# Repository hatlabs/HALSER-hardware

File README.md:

# Hat Labs Serial Interface Device (HALSER)

This repository contains the Hat Labs Serial Interface Device (HALSER) hardware design. HALSER is a powerful microcontroller development board designed for marine environments that allows interfacing with legacy NMEA 0183, RS-232 and UART devices.

Since the board has native WiFi and NMEA 2000 compatible CAN bus connectivity, it can be used to create boards with either Signal K or native NMEA 2000 connectivity (or both!).

## Features

The main design features include:

- Built around ESP32-C3, a powerful 32-bit microcontroller with 4 MB of flash
- Wide-range 5-32 V power input with surge protection
- NMEA 2000 compatible CAN interface (4-pin pluggable terminal block screw connector)
- One transmitting and one receiving RS-485 interface for bidirectional communication with NMEA 0183 devices (3-pin pluggable terminal block screw connectors)
- One RS-232 interface for communication with legacy devices (3-pin pluggable terminal block screw connector)
- One UART interface for general-purpose communication (3-pin pluggable terminal block screw connector). UART is 5V tolerant and the output voltage can be set to 3.3V or 5V with a jumper.
- 1-Wire interface (3-pin 2.54 mm header)
- I2C interface with a 4-pin 2.54 mm header
- USB type C interface for programming and serial communication
- All above interfaces with proper electromagnetic compatibilty (EMC) design -- the device won't interfere with navigational devices or radio equipment
- All available general-purpose input/output (GPIO) pins broken out to a separate header
- Board designed to fit low-cost waterproof 100x68x50 mm enclosures

Rendering of a version 1.0.0 board:

<!--
Front side.

Back side.

-->

## Getting HALSER

HALSER will be available for purchase at the [Hat Labs web store](https://shop.hatlabs.fi/).

## Documentation

HALSER documentation will be available at the [project GitHub Pages](https://docs.hatlabs.fi/halser/).

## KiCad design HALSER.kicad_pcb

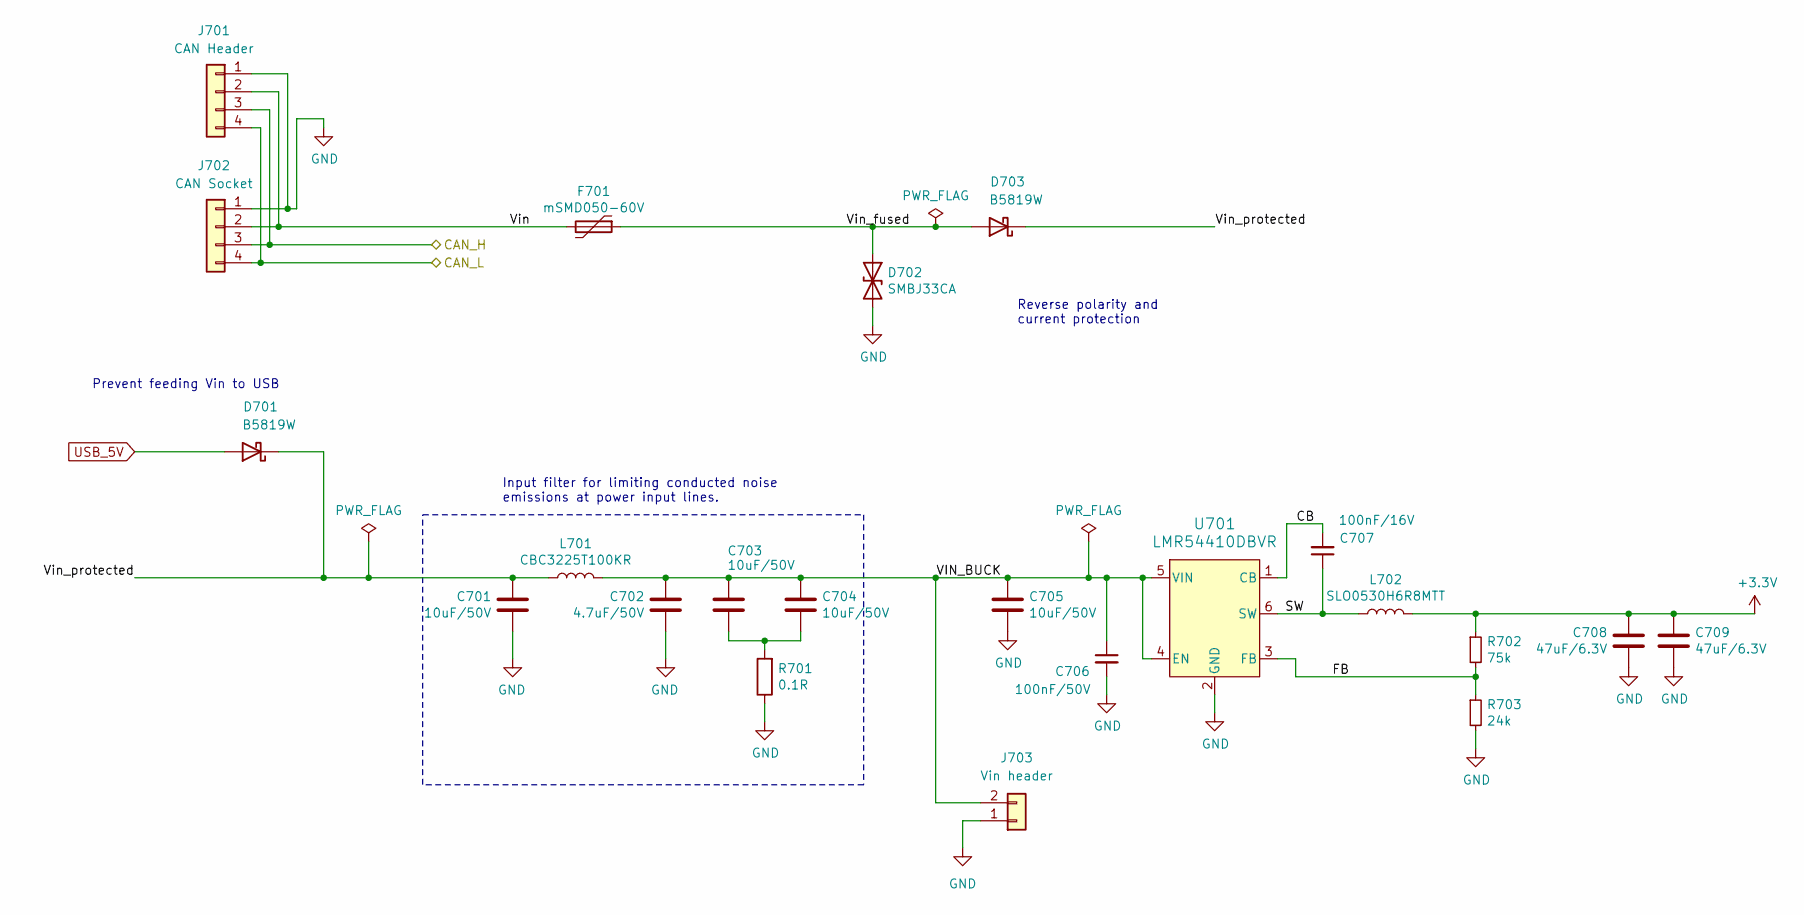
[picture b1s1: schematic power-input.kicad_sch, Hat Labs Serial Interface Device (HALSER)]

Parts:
C701, C703, C704, C705: 10uF/50V; C_1206_3216Metric; LCSC C13585
C702: 4.7uF/50V; C_0805_2012Metric; LCSC C1710
C706: 100nF/50V; C_0603_1608Metric; LCSC C14663
C707: 100nF/16V; C_0402_1005Metric; LCSC C1525
C708, C709: 47uF/6.3V; C_0805_2012Metric; LCSC C16780
D701, D703: B5819W; D_SOD-123; LCSC C8598
D702: SMBJ33CA; D_SMB; LCSC C114000
F701: mSMD050-60V; Fuse_1812_4532Metric; LCSC C70113
J701: CAN Header; PinHeader_1x04_P2.54mm_Vertical; LCSC C7430360
J702: CAN Socket; PhoenixContact_MCV_1,5_4-G-3.81_1x04_P3.81mm_Vertical; LCSC C8410
J703: Vin header; PinHeader_1x02_P2.54mm_Vertical; LCSC C492401
L701: CBC3225T100KR; L_1210_3225Metric; LCSC C90321
L702: SLO0530H6R8MTT; L_Chilisin_BMRA00050530; LCSC C325965
R701: 0.1R; R_0603_1608Metric; LCSC C3013345
R702: 75k; R_0402_1005Metric; LCSC C208939
R703: 24k; R_0402_1005Metric; LCSC C25769
U701: LMR54410DBVR; SOT-23-6; LCSC C3200265

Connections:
+3.3V: C708.1, C709.1, L702.2, R702.1; also elsewhere on the board
/CAN_H: J701.3, J702.3; also elsewhere on the board
/CAN_L: J701.4, J702.4; also elsewhere on the board
/Power input/CB: C707.2, U701.1 (CB)
/Power input/FB: R702.2, R703.1, U701.3 (FB)
/Power input/SW: C707.1, L702.1, U701.6 (SW)
/Power input/VIN_BUCK: C702.2, C703.1, C704.1, C705.1, C706.1, J703.2, L701.2, U701.4 (EN), U701.5 (VIN)
/Power input/Vin: F701.2, J701.2, J702.2
/Power input/Vin_fused: D702.1 (A1), D703.2 (A), F701.1
/Power input/Vin_protected: C701.1, D701.1 (K), D703.1 (K), L701.1
GND: C701.2, C702.1, C705.2, C706.2, C708.2, C709.2, D702.2 (A2), J701.1, J702.1, J703.1, R701.1, R703.2, U701.2 (GND); also elsewhere on the board
unnamed: C703.2, C704.2, R701.2
USB_5V: D701.2 (A); also elsewhere on the board

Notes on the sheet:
Input filter for limiting conducted noise emissions at power input lines.
Prevent feeding Vin to USB
Reverse polarity and current protection

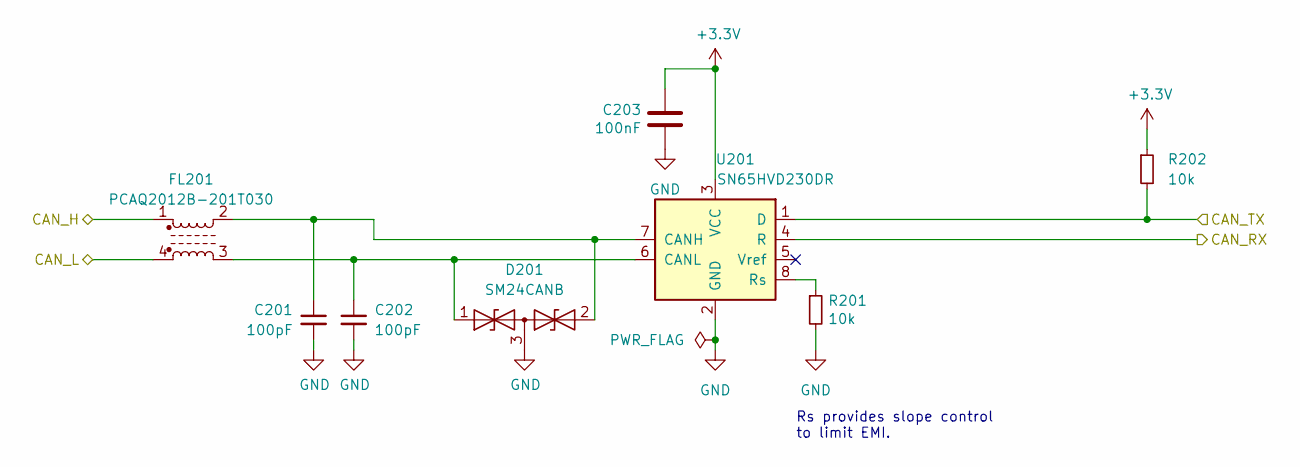
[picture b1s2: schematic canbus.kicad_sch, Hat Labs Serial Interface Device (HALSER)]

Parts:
C201, C202: 100pF; C_0603_1608Metric; LCSC C14858
C203: 100nF; C_0402_1005Metric; LCSC C1525
D201: SM24CANB; SOT-23; LCSC C19185908
FL201: PCAQ2012B-201T030; L_CommonModeChoke_PCAQ2012B; LCSC C2926967
R201, R202: 10k; R_0402_1005Metric; LCSC C25744
U201: SN65HVD230DR; SOIC-8_3.9x4.9mm_P1.27mm; LCSC C12084

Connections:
+3.3V: C203.1, R202.1, U201.3 (VCC); also elsewhere on the board
/CAN_H: FL201.1; also elsewhere on the board
/CAN_L: FL201.4; also elsewhere on the board
/CAN_RX: U201.4 (R); also elsewhere on the board
/CAN_TX: R202.2, U201.1 (D); also elsewhere on the board
GND: C201.2, C202.2, C203.2, D201.3 (common), R201.2, U201.2 (GND); also elsewhere on the board
unnamed: C202.1, D201.1 (A1), FL201.3, U201.6 (CANL)
unnamed: C201.1, D201.2 (A2), FL201.2, U201.7 (CANH)
unnamed: R201.1, U201.8 (Rs)

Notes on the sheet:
Rs provides slope control to limit EMI.

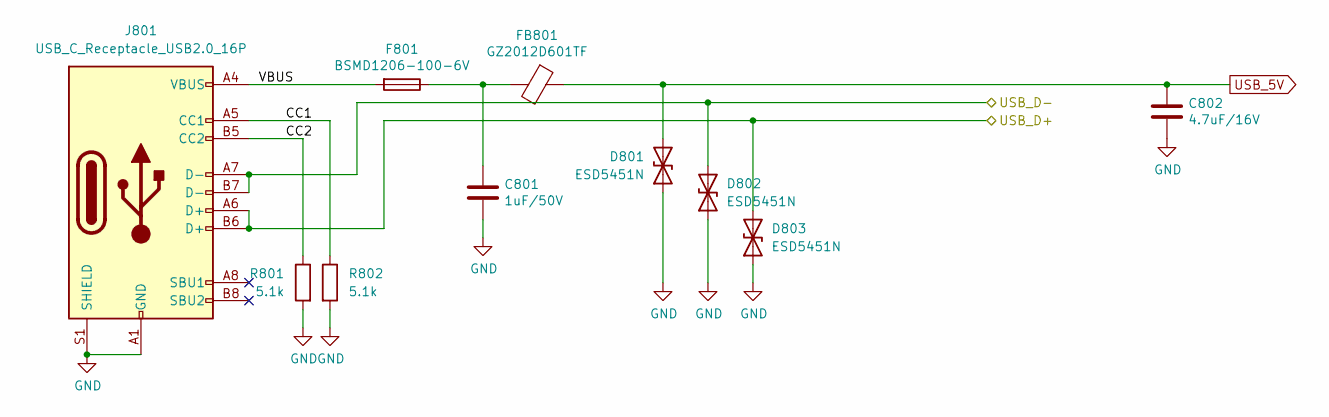
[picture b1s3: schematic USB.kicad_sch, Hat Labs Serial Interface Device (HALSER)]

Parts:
C801: 1uF/50V; C_0603_1608Metric; LCSC C15849
C802: 4.7uF/16V; C_0603_1608Metric; LCSC C19666
D801, D802, D803: ESD5451N; D_0402_1005Metric; LCSC C2936977
F801: BSMD1206-100-6V; Fuse_1206_3216Metric; LCSC C883129
FB801: GZ2012D601TF; L_0805_2012Metric; LCSC C1017
J801: USB_C_Receptacle_USB2.0_16P; Shou Han Type-C 16P LTH6.8; LCSC C5187468
R801, R802: 5.1k; R_0402_1005Metric; LCSC C25905

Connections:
/USB/CC1: J801.A5 (CC1), R802.1
/USB/CC2: J801.B5 (CC2), R801.1
/USB/VBUS: F801.2, J801.A4 (VBUS), J801.A9 (VBUS), J801.B4 (VBUS), J801.B9 (VBUS)
/USB_D+: D803.2 (A2), J801.A6 (D+), J801.B6 (D+); also elsewhere on the board
/USB_D-: D802.2 (A2), J801.A7 (D-), J801.B7 (D-); also elsewhere on the board
GND: C801.2, C802.2, D801.1 (A1), D802.1 (A1), D803.1 (A1), J801.A1 (GND), J801.A12 (GND), J801.B1 (GND), J801.B12 (GND), J801.S1 (SHIELD), R801.2, R802.2; also elsewhere on the board
unnamed: C801.1, F801.1, FB801.2
USB_5V: C802.1, D801.2 (A2), FB801.1; also elsewhere on the board

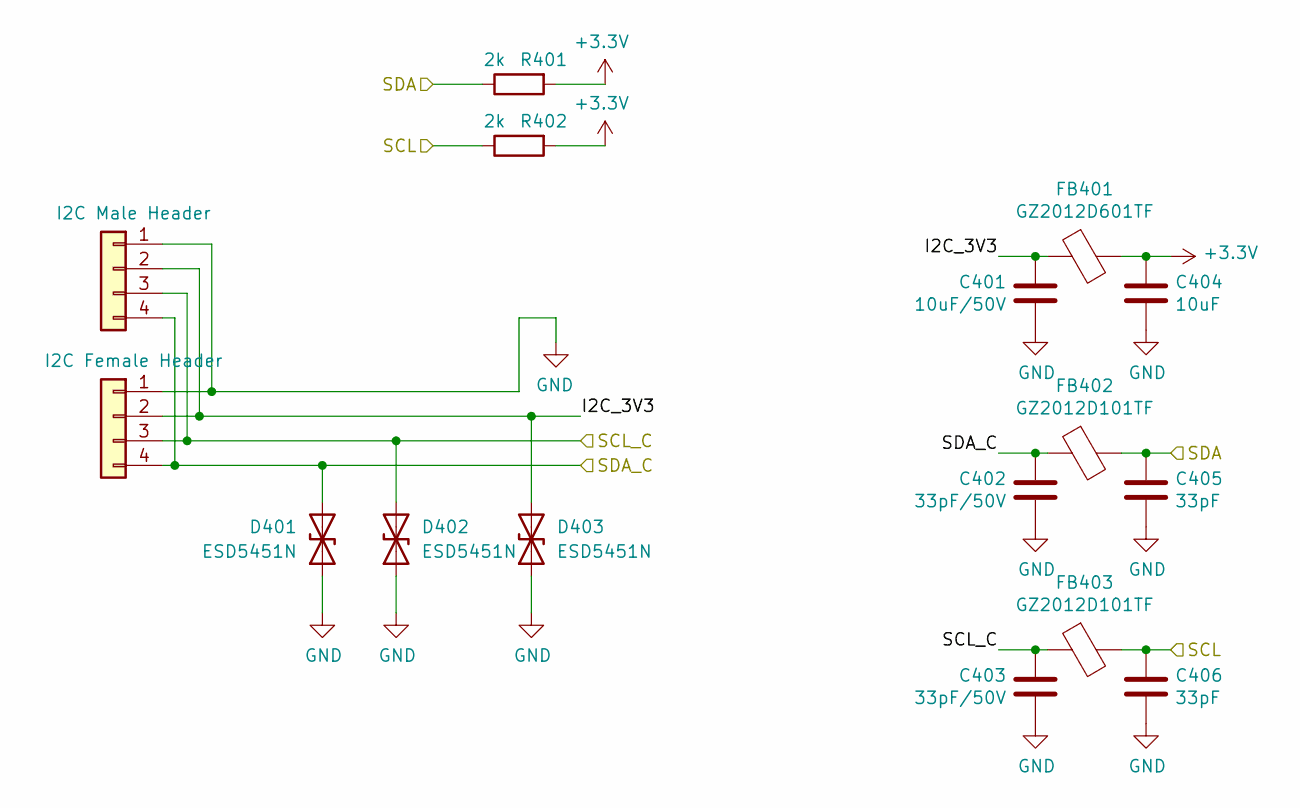
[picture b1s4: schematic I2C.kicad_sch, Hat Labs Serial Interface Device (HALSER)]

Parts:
C401: 10uF/50V; C_1206_3216Metric; LCSC C13585
C402, C403: 33pF/50V; C_0603_1608Metric; LCSC C1663
C404: 10uF; C_0603_1608Metric; LCSC C19702
C405, C406: 33pF; C_0402_1005Metric; LCSC C1562
D401, D402, D403: ESD5451N; D_0402_1005Metric; LCSC C2936977
FB401: GZ2012D601TF; L_0805_2012Metric; LCSC C1017
FB402, FB403: GZ2012D101TF; L_0805_2012Metric; LCSC C1015
J401: I2C Male Header; PinHeader_1x04_P2.54mm_Vertical; LCSC C6332197
J402: I2C Female Header; PinSocket_1x04_P2.54mm_Vertical; LCSC C2718488
R401, R402: 2k; R_0402_1005Metric; LCSC C4109

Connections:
+3.3V: C404.1, FB401.2, R401.2, R402.2; also elsewhere on the board
/I2C/I2C_3V3: C401.1, D403.2 (A2), FB401.1, J401.2, J402.2
/SCL: C406.1, FB403.2, R402.1; also elsewhere on the board
/SCL_C: C403.1, D402.2 (A2), FB403.1, J401.3, J402.3; also elsewhere on the board
/SDA: C405.1, FB402.2, R401.1; also elsewhere on the board
/SDA_C: C402.1, D401.2 (A2), FB402.1, J401.4, J402.4; also elsewhere on the board
GND: C401.2, C402.2, C403.2, C404.2, C405.2, C406.2, D401.1 (A1), D402.1 (A1), D403.1 (A1), J401.1, J402.1; also elsewhere on the board

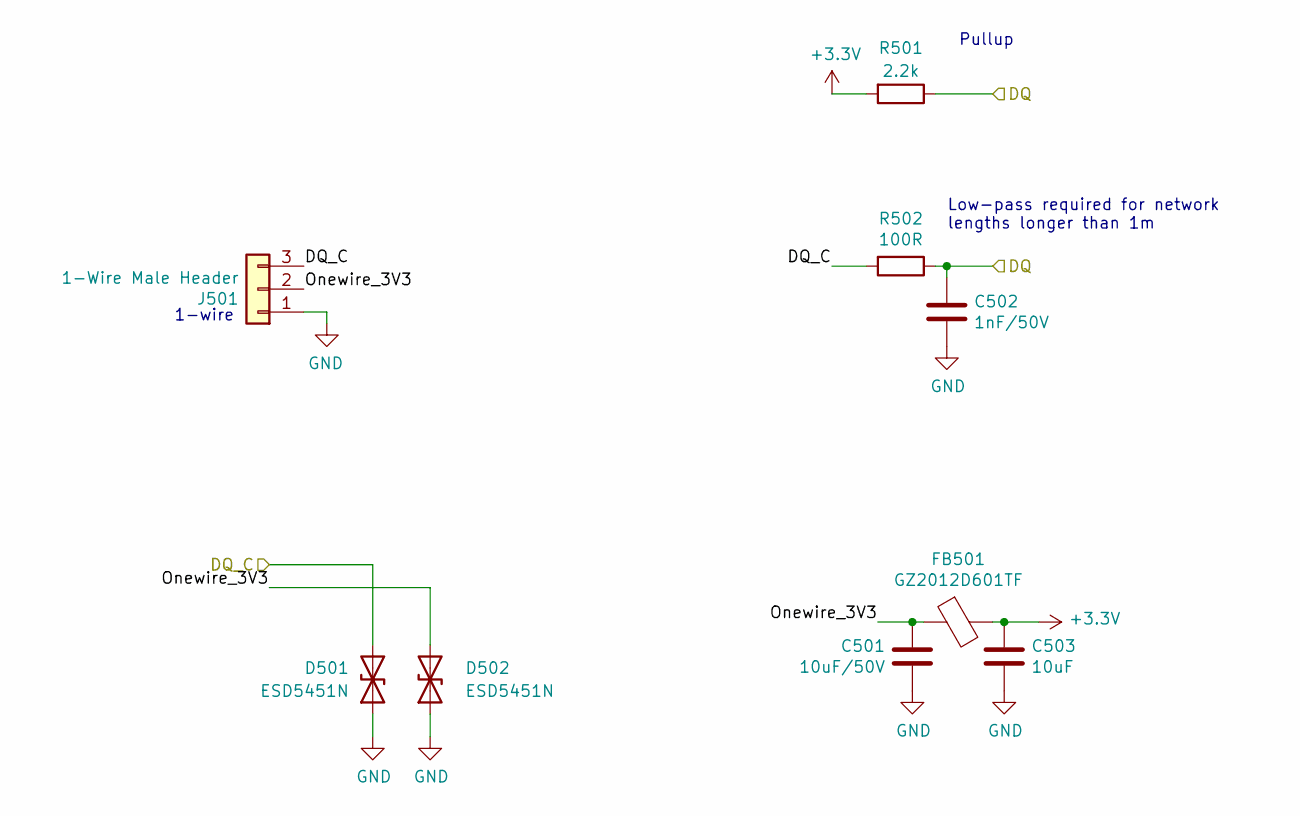
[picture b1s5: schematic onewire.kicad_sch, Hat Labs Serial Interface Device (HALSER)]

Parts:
C501: 10uF/50V; C_1206_3216Metric; LCSC C13585
C502: 1nF/50V; C_0603_1608Metric; LCSC C1588
C503: 10uF; C_0603_1608Metric; LCSC C19702
D501, D502: ESD5451N; D_0402_1005Metric; LCSC C2936977
FB501: GZ2012D601TF; L_0805_2012Metric; LCSC C1017
J501: 1-Wire Male Header; PinHeader_1x03_P2.54mm_Vertical; LCSC C49257
R501: 2.2k; R_0402_1005Metric; LCSC C25879
R502: 100R; R_0805_2012Metric; LCSC C17408

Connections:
+3.3V: C503.1, FB501.2, R501.2; also elsewhere on the board
/DQ: C502.1, R501.1, R502.1; also elsewhere on the board
/DQ_C: D501.2 (A2), J501.3, R502.2; also elsewhere on the board
/Onewire/Onewire_3V3: C501.1, D502.2 (A2), FB501.1, J501.2
GND: C501.2, C502.2, C503.2, D501.1 (A1), D502.1 (A1), J501.1; also elsewhere on the board

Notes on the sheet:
1-wire
Low-pass required for network lengths longer than 1m
Pullup

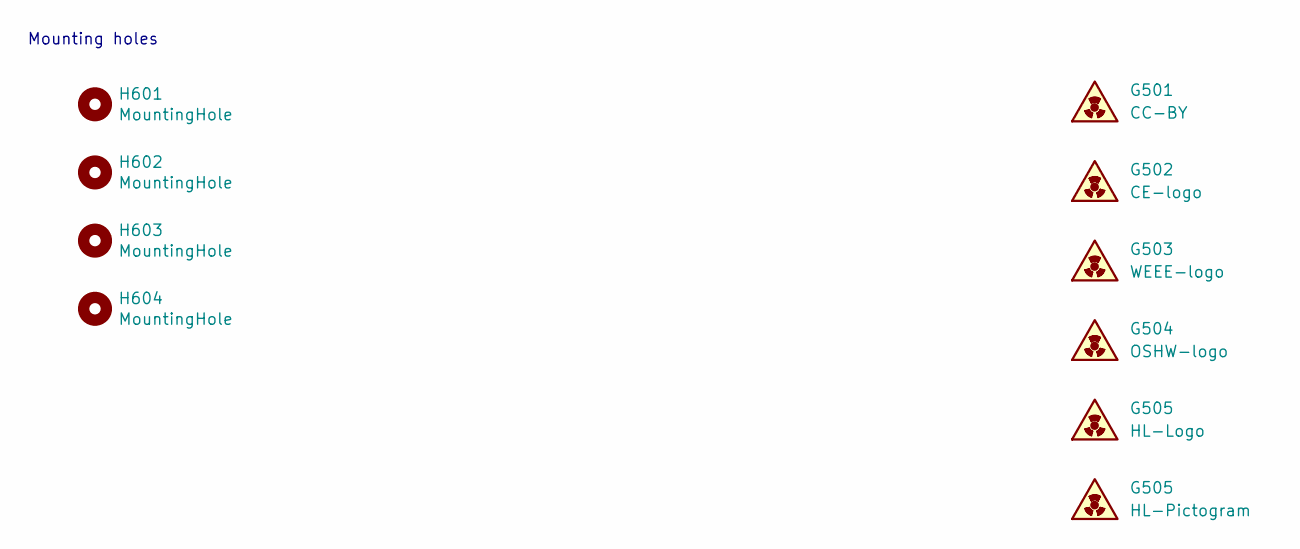
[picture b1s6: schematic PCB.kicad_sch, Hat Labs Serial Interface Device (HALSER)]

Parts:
G501: CC-BY; cc-by_5mm
G502: CE-logo; CE-Logo_11.2x8mm_SilkScreen
G503: WEEE-logo; WEEE-Logo_5.6x8mm_SilkScreen
G504: OSHW-logo; OSHW-Logo2_9.8x8mm_SilkScreen
G505: HL-Logo; Hat_Labs_25.4mm
H601, H602, H603, H604: MountingHole; MountingHole_3.2mm_M3_ISO7380

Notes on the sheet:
Mounting holes

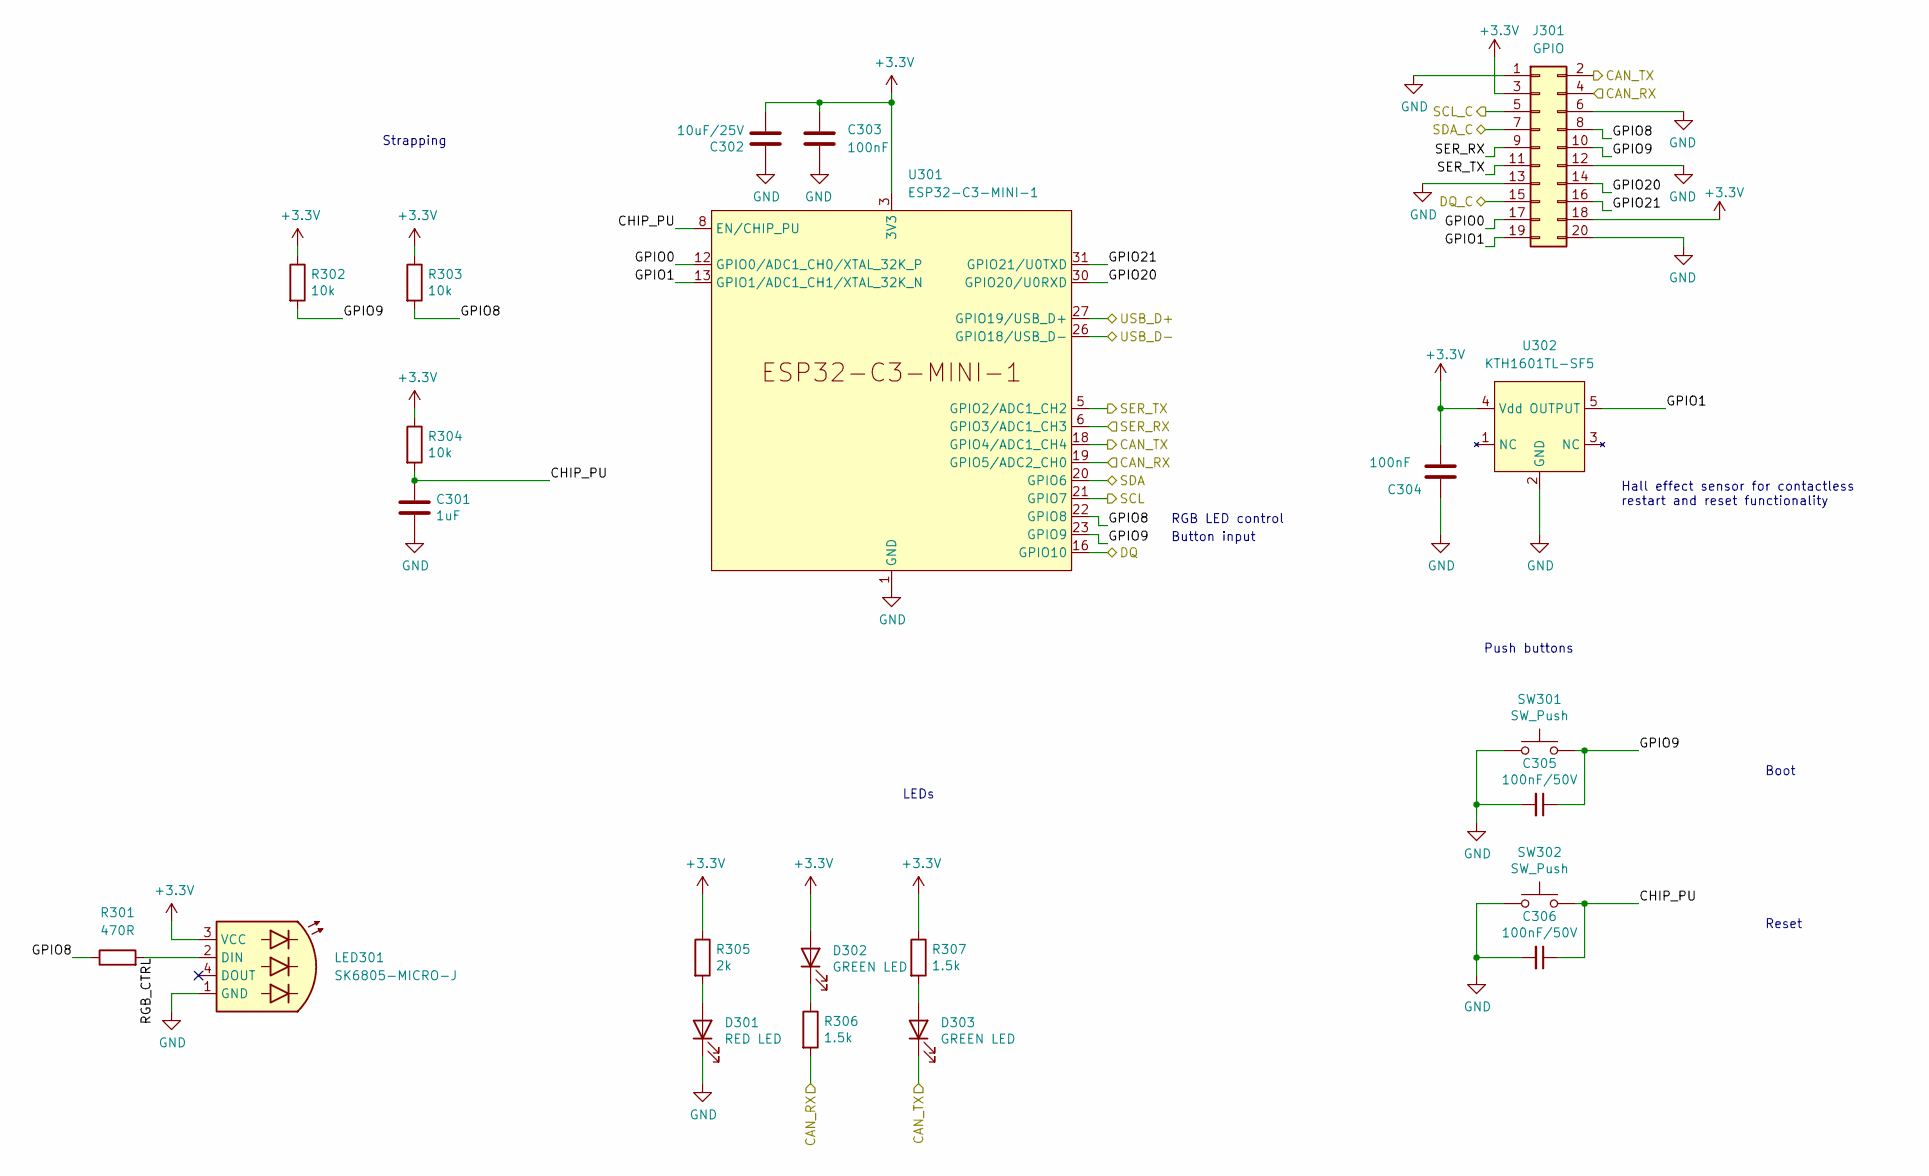
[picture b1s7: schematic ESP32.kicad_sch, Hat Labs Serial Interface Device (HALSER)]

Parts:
C301: 1uF; C_0402_1005Metric; LCSC C52923
C302: 10uF/25V; C_0805_2012Metric; LCSC C15850
C303, C304: 100nF; C_0402_1005Metric; LCSC C1525
C305, C306: 100nF/50V; C_0603_1608Metric; LCSC C14663
D301: RED LED; LED_0603_1608Metric; LCSC C2286
D302, D303: GREEN LED; LED_0603_1608Metric; LCSC C965804
J301: GPIO; PinHeader_2x10_P2.54mm_Vertical; LCSC C7501600
LED301: SK6805-MICRO-J; LED_SK6805_PLCC4_2.4x2.7mm_P1.3mm; LCSC C2909056
R301: 470R; R_0603_1608Metric
R302, R303, R304: 10k; R_0402_1005Metric; LCSC C25744
R305: 2k; R_0402_1005Metric; LCSC C4109
R306, R307: 1.5k; R_0402_1005Metric; LCSC C25867
SW301, SW302: SW_Push; SW_SPST_TL3342; LCSC C318887
U301: ESP32-C3-MINI-1; LCSC C2934569
U302: KTH1601TL-SF5; SOT-553; LCSC C962140

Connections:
+3.3V: C302.2, C303.1, C304.2, D302.2 (A), J301.3, J301.18, LED301.3 (VCC), R302.1, R303.1, R304.1, R305.1, R307.1, U301.3 (3V3), U302.4 (Vdd); also elsewhere on the board
/CAN_RX: J301.4, R306.2, U301.19 (GPIO5/ADC2_CH0); also elsewhere on the board
/CAN_TX: D303.1 (K), J301.2, U301.18 (GPIO4/ADC1_CH4); also elsewhere on the board
/DQ: U301.16 (GPIO10); also elsewhere on the board
/DQ_C: J301.15; also elsewhere on the board
/ESP32/CHIP_PU: C301.1, C306.1, R304.2, SW302.2, U301.8 (EN/CHIP_PU)
/ESP32/GPIO0: J301.17, U301.12 (GPIO0/ADC1_CH0/XTAL_32K_P)
/ESP32/GPIO1: J301.19, U301.13 (GPIO1/ADC1_CH1/XTAL_32K_N), U302.5 (OUTPUT)
/ESP32/GPIO8: J301.8, R301.1, R303.2, U301.22 (GPIO8)
/ESP32/GPIO9: C305.1, J301.10, R302.2, SW301.2, U301.23 (GPIO9)
/ESP32/GPIO20: J301.14, U301.30 (GPIO20/U0RXD)
/ESP32/GPIO21: J301.16, U301.31 (GPIO21/U0TXD)
/ESP32/RGB_CTRL: LED301.2 (DIN), R301.2
/SCL: U301.21 (GPIO7); also elsewhere on the board
/SCL_C: J301.7; also elsewhere on the board
/SDA: U301.20 (GPIO6); also elsewhere on the board
/SDA_C: J301.5; also elsewhere on the board
/SER_RX: J301.9, U301.6 (GPIO3/ADC1_CH3); also elsewhere on the board
/SER_TX: J301.11, U301.5 (GPIO2/ADC1_CH2); also elsewhere on the board
/USB_D+: U301.27 (GPIO19/USB_D+); also elsewhere on the board
/USB_D-: U301.26 (GPIO18/USB_D-); also elsewhere on the board
GND: C301.2, C302.1, C303.2, C304.1, C305.2, C306.2, D301.1 (K), J301.1, J301.6, J301.12, J301.13, J301.20, LED301.1 (GND), SW301.1, SW302.1, U301.1 (GND), U301.2 (GND), U301.11 (GND), U301.14 (GND), U301.36 (GND), U301.37 (GND), U301.38 (GND), U301.39 (GND), U301.40 (GND), U301.41 (GND), U301.42 (GND), U301.43 (GND), U301.44 (GND), U301.45 (GND), U301.46 (GND), U301.47 (GND), U301.48 (GND), U301.49 (GND), U301.50 (GND), U301.51 (GND), U301.52 (GND), U301.53 (GND), U302.2 (GND); also elsewhere on the board
unnamed: D301.2 (A), R305.2
unnamed: D302.1 (K), R306.1
unnamed: D303.2 (A), R307.2

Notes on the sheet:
Hall effect sensor for contactless restart and reset functionality
Button input
Strapping
RGB LED control
Reset
Boot
LEDs
Push buttons

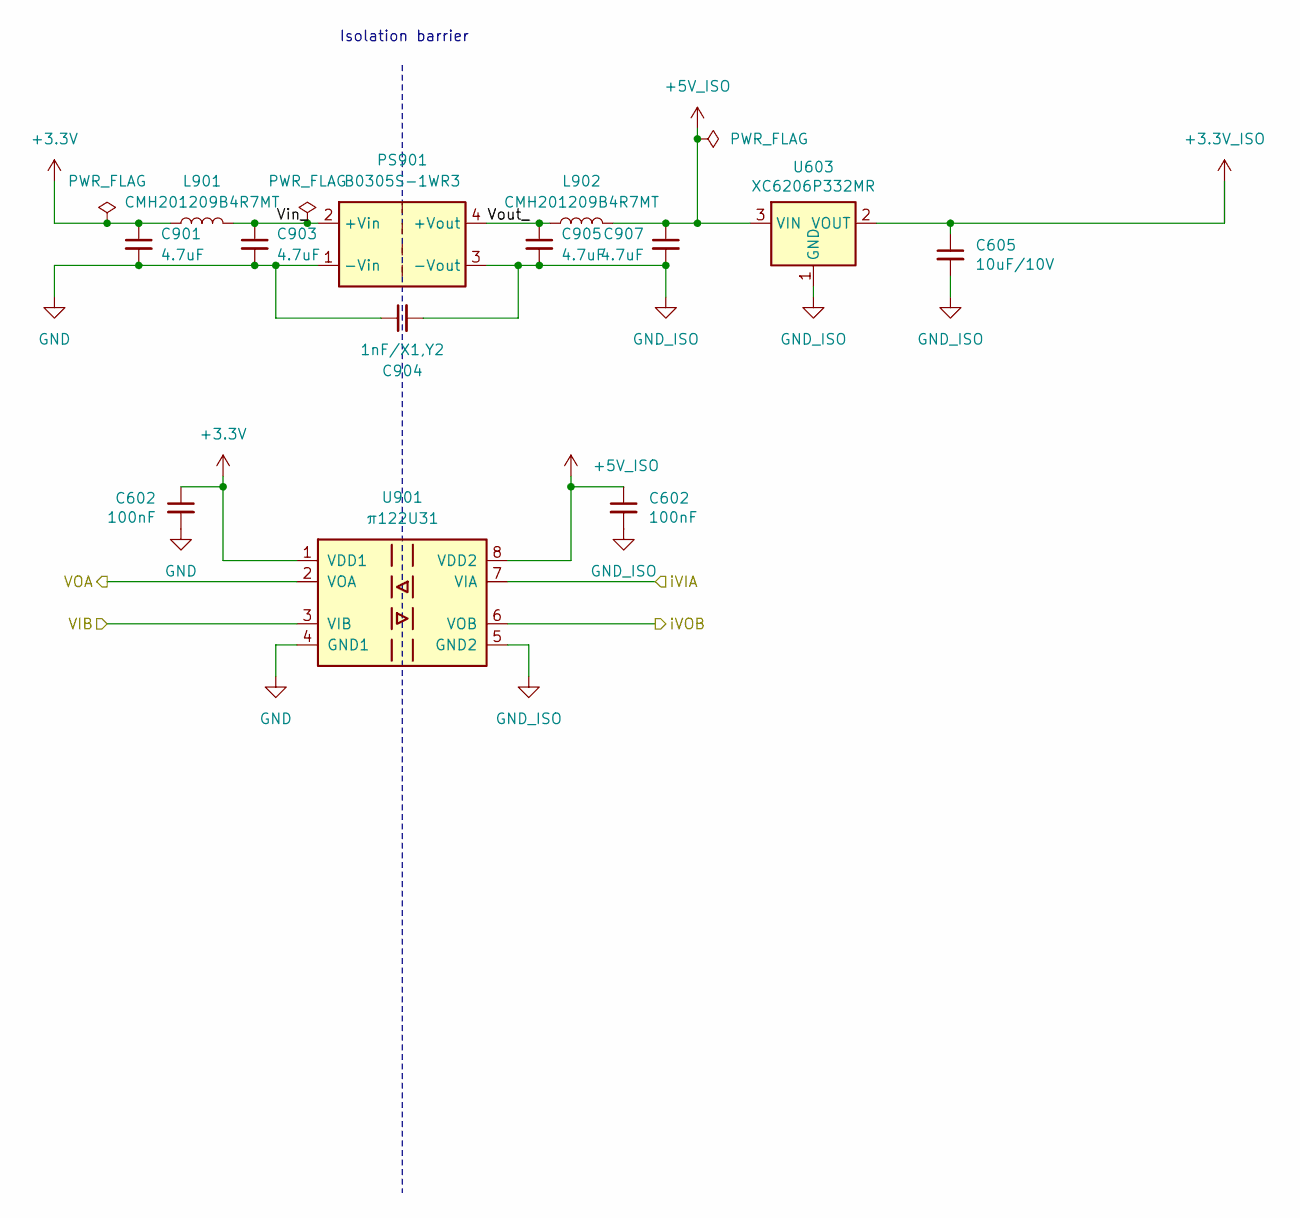
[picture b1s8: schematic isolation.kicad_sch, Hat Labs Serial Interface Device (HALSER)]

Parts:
C602: 100nF; C_0402_1005Metric; LCSC C1525
C605: 10uF/10V; C_0603_1608Metric; LCSC C19702
C901, C903, C905, C907: 4.7uF; C_0603_1608Metric; LCSC C19666
C904: 1nF/X1,Y2; C_1808_4520Metric; LCSC C784081
L901, L902: CMH201209B4R7MT; L_0805_2012Metric; LCSC C394959
PS901: B0305S-1WR3; Converter_DCDC_Murata_MEE1SxxxxSC_THT; LCSC C7465186
U603: XC6206P332MR; SOT-23; LCSC C5446
U901: π122U31; SOIC-8_3.9x4.9mm_P1.27mm; LCSC C471590

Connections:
+3.3V: C901.1, L901.1, U901.1 (VDD1); also elsewhere on the board
+5V_ISO: C907.1, L902.2, U901.8 (VDD2); also elsewhere on the board
/Isolation barrier/Vin_: C903.1, L901.2, PS901.2 (+Vin)
/Isolation barrier/Vout_: C905.1, L902.1, PS901.4 (+Vout)
/Isolation barrier/iVIA: U901.7 (VIA); also elsewhere on the board
/Isolation barrier/iVOB: U901.6 (VOB); also elsewhere on the board
/SER_RX: U901.2 (VOA); also elsewhere on the board
/SER_TX: U901.3 (VIB); also elsewhere on the board
GND: C901.2, C903.2, C904.1, PS901.1 (-Vin), U901.4 (GND1); also elsewhere on the board
GND_ISO: C904.2, C905.2, C907.2, PS901.3 (-Vout), U901.5 (GND2); also elsewhere on the board

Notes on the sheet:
Isolation barrier

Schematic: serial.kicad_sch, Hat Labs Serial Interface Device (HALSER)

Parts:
C1001, C1002, C1003, C1004, C1005, C1006, C1007, C1008: 100nF; C_0402_1005Metric; LCSC C1525
C1009, C1010, C1011, C1012, C1015, C1016, C1017, C1018: 100pF; C_0603_1608Metric; LCSC C14858
C1013, C1014, C1019, C1020: 150pF/50V; C_0603_1608Metric; LCSC C1594
D1001, D1002: GREEN LED; LED_0603_1608Metric; LCSC C965804
D1003, D1004: SM712_SOT23; SOT-23; LCSC C521963
D1005: PESD15VS2UT; SOT-23; LCSC C2831524
D1006, D1009: ESD5451N; D_0402_1005Metric; LCSC C2936977
D1007, D1008: SMAJ16CA; D_SMA; LCSC C5356049
F1001, F1002, F1003, F1004: nSMD005/60V; Fuse_1206_3216Metric; LCSC C2830235
FB1001, FB1002, FB1003, FB1004: GZ2012D601TF; L_0805_2012Metric; LCSC C1017
FL1001, FL1002: PCAQ2012B-201T030; L_CommonModeChoke_PCAQ2012B; LCSC C2926967
J1001: RX Sel Header; PinHeader_2x03_P2.54mm_Vertical; LCSC C5383104
J1002: RS485 RX Socket; PhoenixContact_MCV_1,5_3-G-3.81_1x03_P3.81mm_Vertical; LCSC C8389
J1003: RS485 TX Socket; PhoenixContact_MCV_1,5_3-G-3.81_1x03_P3.81mm_Vertical; LCSC C8389
J1004: RS-232 Socket; PhoenixContact_MCV_1,5_3-G-3.81_1x03_P3.81mm_Vertical; LCSC C8389
J1005: UART Socket; PhoenixContact_MCV_1,5_3-G-3.81_1x03_P3.81mm_Vertical; LCSC C8389
JP1001: UART V-sel; PinHeader_1x03_P2.54mm_Vertical
R1001, R1002: 2.2k; R_0402_1005Metric
R1003, R1004, R1005, R1006: 10R; R_0402_1005Metric; LCSC C25077
R1007, R1008: 51R; R_0603_1608Metric; LCSC C23197
R1009, R1010: 470R; R_0603_1608Metric; LCSC C23179
U1001: 74LVC2G17; SOT-23-6; LCSC C10429
U1002, U1004: SN75176BDR; SOIC-8_3.9x4.9mm_P1.27mm; LCSC C2829048
U1003: SP3232EEY-L/TR; TSSOP-16_4.4x5mm_P0.65mm; LCSC C13482

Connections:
+3.3V_ISO: JP1001.1 (A); also elsewhere on the board
+5V_ISO: C1001.2, C1002.2, C1003.2, JP1001.3 (B), R1001.1, R1002.1, U1002.8 (VCC), U1003.8 (R2IN), U1003.10 (T2IN), U1003.16 (VCC), U1004.2 (~RE), U1004.3 (DE), U1004.8 (VCC); also elsewhere on the board
/Isolation barrier/iVIA: D1001.1 (K), J1001.1, J1001.3, J1001.5; also elsewhere on the board
/Isolation barrier/iVOB: D1002.1 (K), U1001.1, U1003.11 (T1IN), U1004.4 (D); also elsewhere on the board
/Serial interfaces/RS232_RX: J1001.4, U1003.12 (R1OUT)
/Serial interfaces/RS232_RX_C: J1004.2, R1008.2
/Serial interfaces/RS232_RX_IN: C1014.1, FB1004.1, U1003.13 (R1IN)
/Serial interfaces/RS232_TX_C: J1004.3, R1007.2
/Serial interfaces/RS232_TX_OUT: C1013.1, FB1003.1, U1003.14 (T1OUT)
/Serial interfaces/RS485_RX: J1001.6, U1002.1 (R)
/Serial interfaces/RS485_RX_A: R1004.1, U1002.6 (A)
/Serial interfaces/RS485_RX_A_C: F1002.1, J1002.2
/Serial interfaces/RS485_RX_B: R1003.1, U1002.7 (B)
/Serial interfaces/RS485_RX_B_C: F1001.1, J1002.3
/Serial interfaces/RS485_TX_A: R1006.1, U1004.6 (A)
/Serial interfaces/RS485_TX_A_C: F1003.1, J1003.3
/Serial interfaces/RS485_TX_B: R1005.1, U1004.7 (B)
/Serial interfaces/RS485_TX_B_C: F1004.1, J1003.2
/Serial interfaces/UART_RX: J1001.2, U1001.4
/Serial interfaces/UART_RX_C: J1005.2, R1010.2
/Serial interfaces/UART_RX_IN: C1012.1, FB1002.1, U1001.3
/Serial interfaces/UART_TX_C: J1005.3, R1009.2
/Serial interfaces/UART_TX_OUT: C1011.1, FB1001.1, U1001.6
/Serial interfaces/Vsel: C1005.1, JP1001.2 (C), U1001.5 (VCC)
GND_ISO: C1001.1, C1002.1, C1003.1, C1005.2, C1007.2, C1008.1, C1009.2, C1010.2, C1011.2, C1012.2, C1013.2, C1014.2, C1015.2, C1016.2, C1017.2, C1018.2, C1019.2, C1020.2, D1003.3 (common), D1004.3 (common), D1005.3 (common), D1006.1 (A1), D1009.1 (A1), J1002.1, J1003.1, J1004.1, J1005.1, U1001.2 (GND), U1002.2 (~RE), U1002.3 (DE), U1002.4 (D), U1002.5 (GND), U1003.15 (GND), U1004.5 (GND); also elsewhere on the board
unnamed: C1009.1, FL1001.1, R1003.2
unnamed: C1010.1, FL1002.1, R1005.2
unnamed: C1015.1, FL1001.4, R1004.2
unnamed: C1016.1, FL1002.4, R1006.2
unnamed: D1001.2 (A), R1001.2
unnamed: D1002.2 (A), R1002.2
unnamed: D1003.1 (A1), D1007.2 (A2), F1001.2, FL1001.2
unnamed: D1003.2 (A2), D1007.1 (A1), F1002.2, FL1001.3
unnamed: D1004.1 (A1), D1008.2 (A2), F1003.2, FL1002.2
unnamed: D1004.2 (A2), D1008.1 (A1), F1004.2, FL1002.3
unnamed: C1019.1, D1005.1 (A1), FB1003.2, R1007.1
unnamed: C1020.1, D1005.2 (A2), FB1004.2, R1008.1
unnamed: C1017.1, D1006.2 (A2), FB1001.2, R1009.1
unnamed: C1018.1, D1009.2 (A2), FB1002.2, R1010.1
unnamed: C1004.1, U1003.1 (C1+)
unnamed: C1004.2, U1003.3 (C1-)
unnamed: C1006.1, U1003.4 (C2+)
unnamed: C1006.2, U1003.5 (C2-)
unnamed: C1008.2, U1003.2 (VS+)
unnamed: C1007.1, U1003.6 (VS-)

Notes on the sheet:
RS-485 TX
UART
RS-232
RX selection
RS-485 RX

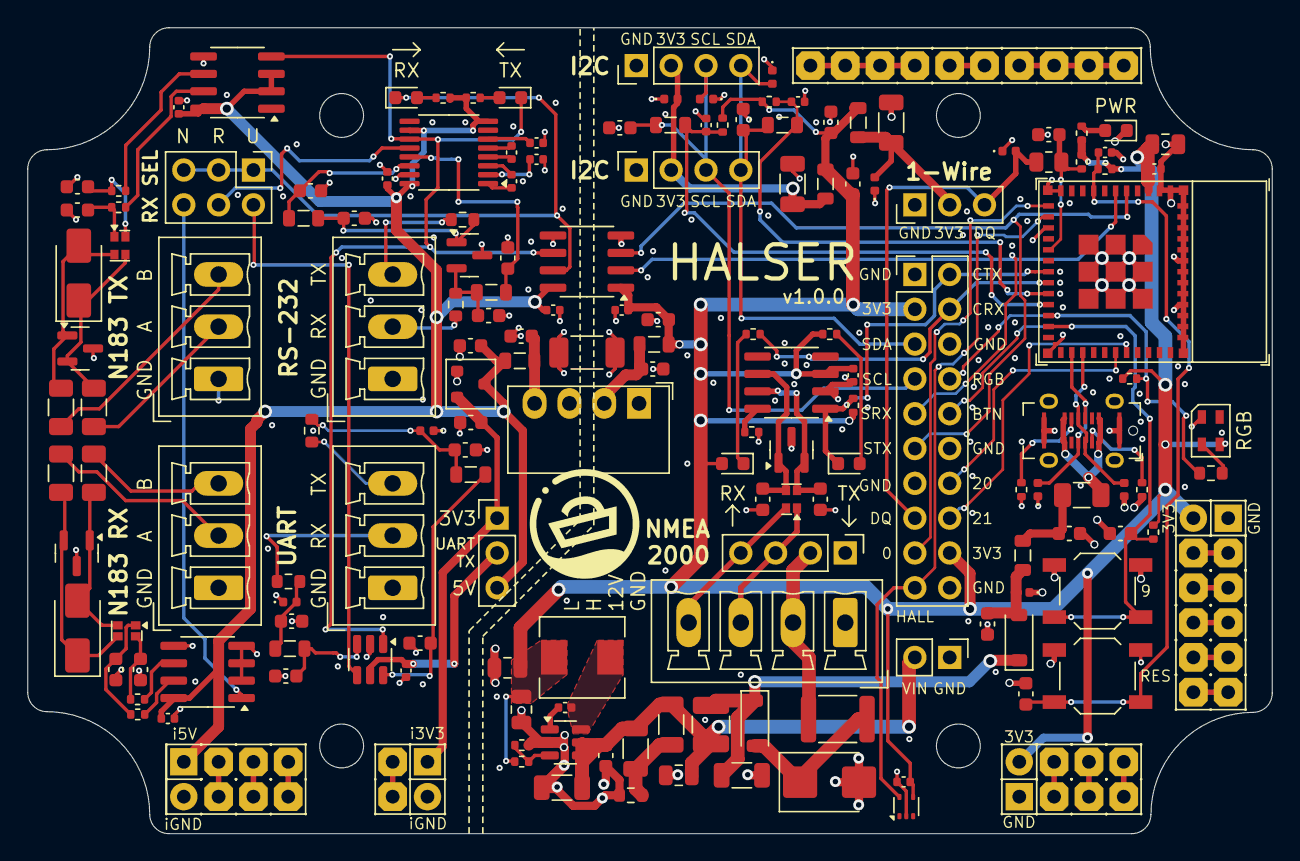
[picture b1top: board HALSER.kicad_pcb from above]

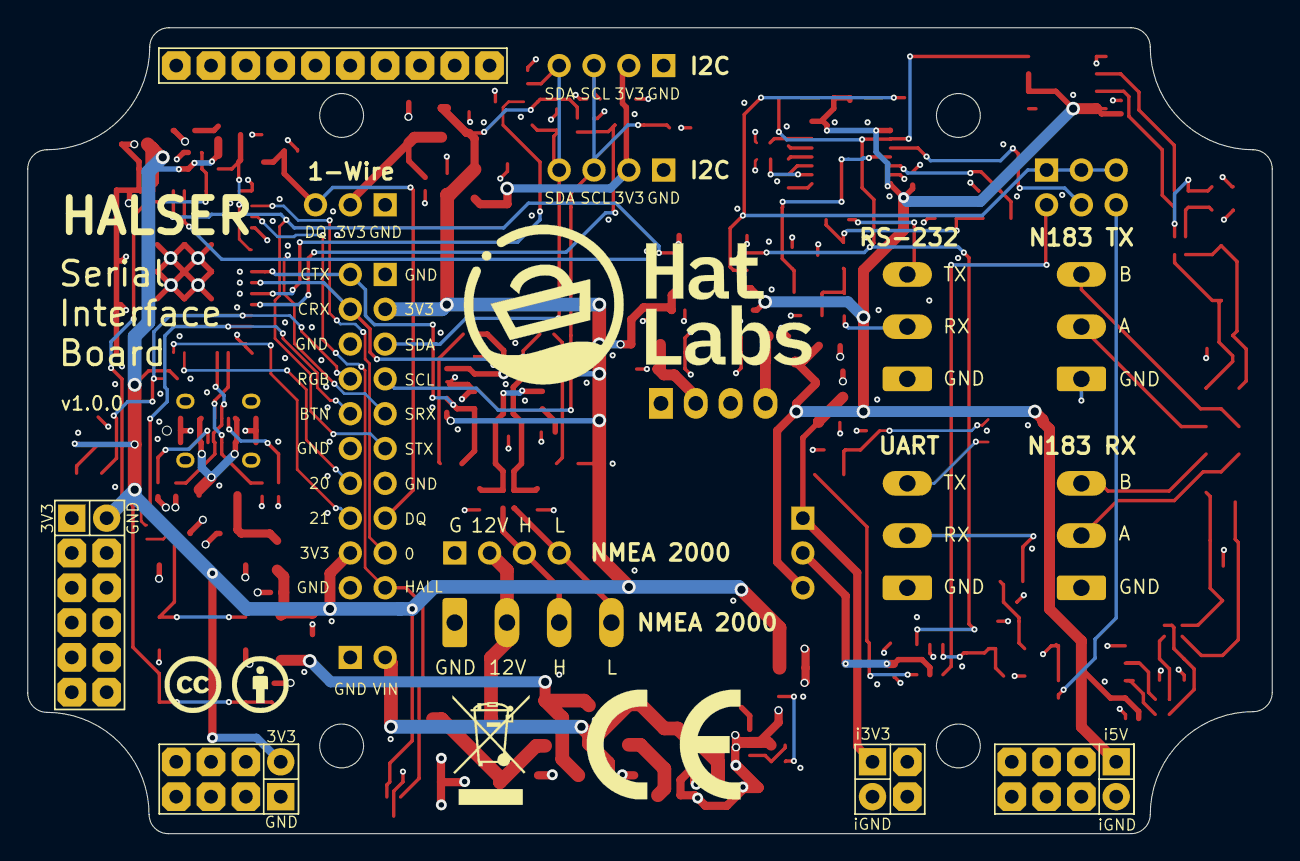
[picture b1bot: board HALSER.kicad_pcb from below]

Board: 4 copper layers, 90.8 x 58.8 mm, 168 parts (4 on the bottom side), 92 nets.

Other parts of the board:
C902, C906: 100nF; C_0402_1005Metric
C908: 10uF/10V; C_0603_1608Metric
G601: CC-BY; cc-by_5mm
G602: CE-logo; CE-Logo_11.2x8mm_SilkScreen
G603: WEEE-logo; WEEE-Logo_5.6x8mm_SilkScreen
G605: HL-Logo; Hat_Labs_25.4mm
G606: HL-Pictogram; HaL_picto_8mm
U902: XC6206P332MR; SOT-23

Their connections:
+3.3V: C902.1; also elsewhere on the board
+3.3V_ISO: C908.1, U902.2 (VOUT); also elsewhere on the board
+5V_ISO: C906.1, U902.3 (VIN); also elsewhere on the board
GND: C902.2; also elsewhere on the board
GND_ISO: C906.2, C908.2, U902.1 (GND); also elsewhere on the board

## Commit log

2024-10-20 Rename HALMET -> HALSER
2024-10-22 Redo schematics
2024-10-24 WIP wiring
2024-10-27 Further design adjustments
2024-10-28 Further manufacturing tweaks
2024-10-28 Update assembly scripts
2024-10-28 FIXUP vias
2024-11-20 Add a hall effect sensor
2024-12-12 Fix issues found in -a1
2024-12-20 Bump versions

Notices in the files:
ESP32.kicad_sch:
https://creativecommons.org/licenses/by-sa/4.0
HALMET is licensed under CC BY-SA 4.0.
